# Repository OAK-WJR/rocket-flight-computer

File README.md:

# Rocket Flight Computer (M3, design only)

> **Status: design only. No board has been built, powered or flown.** Every result below comes from CAD checks, circuit simulation or software tests on a computer, never from hardware.

This is a flight computer for a student high-power rocket. It is one 46 × 238 mm, four-layer circuit board that slides into a 54.66 mm inside-diameter airframe. It runs from a 2-cell LiPo battery, uses an STM32H743 microcontroller, reads an IMU (ICM-45686), a barometer (MS5611) and GPS (SAM-M10Q), logs to flash memory, talks over USB, powers a camera, drives four fin servos for roll control, and has two separately fused circuits to fire the parachute charge. The current design is revision **M3-ASSY-R2** (28 Sep 2026).

*KiCad 3D render of the top side of M3-ASSY-R2 (46 × 238 mm).*

## Demo

There is no video, because the board has not been built. What can be shown and re-run today:

1. **Board checks.** `tools/check.sh` runs KiCad's design-rule check, electrical-rule check and schematic-vs-PCB check. Output on 2026-11-01 (KiCad 10.0.6):
   ```
   DRC violations 0  unconnected 0  schematic parity 0  ERC 0
   metadata / 3D model audit: OK
   ```
2. **Circuit simulation.** The ngspice suite in `m3_design/sim_r2/` found a flaw in the design: with a fresh 8.4 V battery, firing into a shorted igniter pulled the battery below 5 V for 3.9 ms (long enough that the computer could reset and miss the second parachute charge) and pushed 131 A through a transistor rated for 112 A. Adding a 2 Ω pulse resistor to each channel fixed it in simulation (4.1 A, battery stays above 8.2 V).

*Simulated, not measured. Grey: before the fix. Black: with the 2 Ω resistors. The 20 ms pulse length is a rule the future firmware must follow.*

The portfolio page for this project is 8a ("Rocket Flight Computer Design").

## How it works

```mermaid
flowchart LR
  BAT[2S LiPo battery] --> PWR[power switch, reverse and over-voltage protection, 3.3 V supply]
  PWR --> MCU[STM32H743 microcontroller]
  SEN[IMU, barometer, GPS] --> MCU
  MCU --> LOG[flash log]
  MCU --> USB[USB diagnostics]
  MCU --> CAM[camera power and UART]
  BAT --> ACT[actuator power switch]
  ACT --> SRV[four fin servos]
  ACT --> ARM[arming plug: a full break] --> PYRO[two fused parachute channels]
  MCU --> SRV
  MCU --> PYRO
```

- **One board instead of two.** An earlier version split the design into an M1 power/actuator board and an M2 microcontroller/sensor board joined by harnesses; M3 merges them back into one board (one assembly order, no 21-wire harness); the old M1 board is kept in `reference/m1_power_actuator/`.
- **Safety by hardware.** The arming plug is a complete electrical break in the parachute circuit; a script (`m3_design/check_actuators.py`) reads the PCB copper and fails if anything bypasses it.
- **Easy to diagnose.** Test pads, voltage-sense dividers and fault lines on the power rails; the bench firmware (for the previous revision R1) reports them over USB, and the host tools in `diagnostics/` turn a report into a list of likely faults.
- **Every part checked.** All BOM lines were checked against the maker's datasheet for pinout, land pattern, polarity and 3D orientation (`docs/R2_VERIFICATION.md`).

## How to run it

No hardware is needed for any of these. Tested on macOS with KiCad 10.0.6, ngspice 46 and Python 3.9 on 2026-11-01.

```bash
git clone https://github.com/OAK-WJR/rocket-flight-computer.git
cd rocket-flight-computer

tools/check.sh                          # DRC + ERC + schematic parity + 3D/metadata audit (needs KiCad 10.0.x)
python3 m3_design/check_actuators.py    # arming / pyro / servo safety contract -> "actuator safety contract: OK"
python3 m3_design/sim_r2/run.py         # ngspice suite -> {'PASS': 135, 'OLD-FAIL': 6, 'INFO': 8, 'DEMO': 2}
python3 m3_design/sim_r2/plot_short.py  # redraws docs/images/shorted_igniter_sim.png (needs matplotlib)
python3 tools/export_fab.py             # Gerber zip + JLCPCB BOM/CPL into m3_design/assembly_review/fab/

python3 -m venv .venv && .venv/bin/pip install -r diagnostics/requirements-lock.txt
.venv/bin/python -m unittest discover -s diagnostics -t . -p 'test_*.py'      # 173 tests, OK (1 skipped)
(cd m3_firmware && PYTHONPATH=.. python3 -m unittest test_firmware test_gnss test_usb)  # 41 tests, OK

open m3_design/assembly_review/m3.kicad_pro   # open the design in KiCad 10
```

- KiCad must be **10.0.x** (older versions cannot open the files). On Linux/Windows set `KICAD_CLI=/path/to/kicad-cli` before `tools/check.sh`.
- `OLD-FAIL` rows in the simulation are the pre-fix design, kept on purpose for comparison.
- **Firmware build:** `m3_firmware/build.py` needs the Arm GNU Toolchain 15.2.rel1 in `m3_firmware/toolchain/` and the maker datasheet PDFs it hash-checks (not committed, for copyright). It also refuses to build for R2 on purpose, because no R2 firmware exists yet. Prebuilt bench images for the older R1 board are in `m3_firmware/build_assembly_*/`. Do not run them on an R2 board.
- **To make a real board** you would order it from JLCPCB with the files from `tools/export_fab.py` (see `docs/ORDERING.md`), then need a 2S LiPo, an ST-Link/SWD probe and a USB-C cable. None of this has been done.

## Repo layout

| Path | What is in it |
|---|---|
| `m3_design/assembly_review/` | The KiCad 10 project (the single source of truth): 14 schematic sheets, PCB, local footprints, symbols and 3D models, schematic PNG/SVG exports in `sheets/`, review notes |
| `m3_design/sim_r2/` | ngspice suite for the actuator and parachute circuits (`run.py`, `RESULTS.md`, `FINDINGS.md`, `plot_short.py`) |
| `m3_design/check_actuators.py` | Safety check that reads the PCB netlist |
| `m3_firmware/` | Bench diagnostic firmware v0.8.1 (C, STM32 HAL + TinyUSB) for the R1 board, pin bindings, host-side tests |
| `diagnostics/` | Python host tools: USB/SWD readout, log recovery, fault localisation, test-point map |
| `docs/` | Ordering guide, part-by-part verification, actuator merge record, design rationale, FMEA, simulation notes, design history |
| `quality_audit/` | Board audit: conflicting part numbers, 3D model paths, DRC/ERC evidence |
| `reference/` | Older boards kept for comparison: M1 power/actuator board, M3-ASSY-R1 |
| `tools/` | `check.sh` (board gate), `export_fab.py` (fabrication files), JLCPCB stock and orientation helpers |
| `STATUS.md` | Every requirement and what is and is not verified |
| `AGENTS.md`, `CLAUDE.md` | The rules given to the AI coding assistants (see Credits) |

## Results and honest limits

What is done (on a computer only):
- KiCad DRC, ERC and schematic parity all at zero; 183 placed parts, every one with a JLCPCB/LCSC part code.
- 135 simulation checks pass for the current design; the shorted-igniter flaw was found and fixed in simulation.
- 173 host diagnostic tests and 41 firmware host tests pass.

What is not done:
- **Nothing has been ordered, built, powered, measured or flown.** Simulations use datasheet models, not measured parts.
- No firmware exists for R2. The firmware here is bench diagnostics for R1 only; it has no flight logic, servo control or parachute firing.
- Servo stall current through the board (about 7.7 A with all four stalled) is an estimate, not a measurement.
- Fit in the sled and airframe, the arming plug hardware and the external power switch are still open (`STATUS.md`, `docs/R2_VERIFICATION.md` §4).

Other branches: `m3-assy-r11` is the development line. It holds the later redesigns R3 to R10 (Oct 2026) and the compact R11 candidate (Nov 2026), committed by a collaborator, and the R10 bench diagnostics; each earlier revision is in its history. They are not part of the R2 design described here.

## Credits

**Jerry Wu (Jiarui Wu):** the project and its requirements: one board that fits the 54.66 mm airframe, built-in USB diagnostics, at most three PCB iterations. I chose to merge the two earlier boards into one, set the system constraints, made the design decisions recorded as "owner rulings" (for example two independently fused parachute channels, and keeping the backup altimeter fully separate), and reviewed the layout, flagging routing problems such as unwanted zigzag traces.

**AI coding assistants:** they produced most of the schematics, PCB layout, simulations, firmware and scripts from my requirements and decisions.
- **Claude Code** wrote the design documents, drew the first schematics through the EasyEDA API, wrote the KiCad board, routing and check scripts, and ran the ngspice simulations. It proposed and chose the 2 Ω per-channel pulse resistors shown above; I approved them. It also merged pull requests #1–#5 on my account, so those merge commits show my name.
- **Codex** did the quality audit, the single-board versions up to M3-ASSY-R1, the bench firmware v0.1–v0.8.1 and the USB diagnostic tools.
- Commits made with Claude Code carry a `Co-Authored-By: Claude` line. `AGENTS.md` (read by Codex, and by Claude Code through `CLAUDE.md`) holds the safety and routing rules they had to follow.

**Collaborator and existing work:**
- **Ethan Huang** (collaborator) merged the four servo outputs, the two fused parachute channels with the arming break, the pull-pin and the buzzer into the board (pull request #1, 26 Sep 2026), also with Claude Code. He committed the later R3–R10 branches.
- **Open-source code and models:** TinyUSB (MIT), STM32CubeH7 HAL (BSD-3-Clause) and CMSIS headers (Apache-2.0) in `m3_firmware/vendor/`; KiCad library 3D models (CC-BY-SA 4.0 with exception); footprints and 3D models converted from the EasyEDA/LCSC library with easyeda2kicad. Details and licences: [THIRD_PARTY_NOTICES.md](THIRD_PARTY_NOTICES.md).
- **Tools:** KiCad 10, ngspice, Python, Arm GNU Toolchain; part data from maker datasheets and LCSC/JLCPCB pages (linked in the review notes, not copied).

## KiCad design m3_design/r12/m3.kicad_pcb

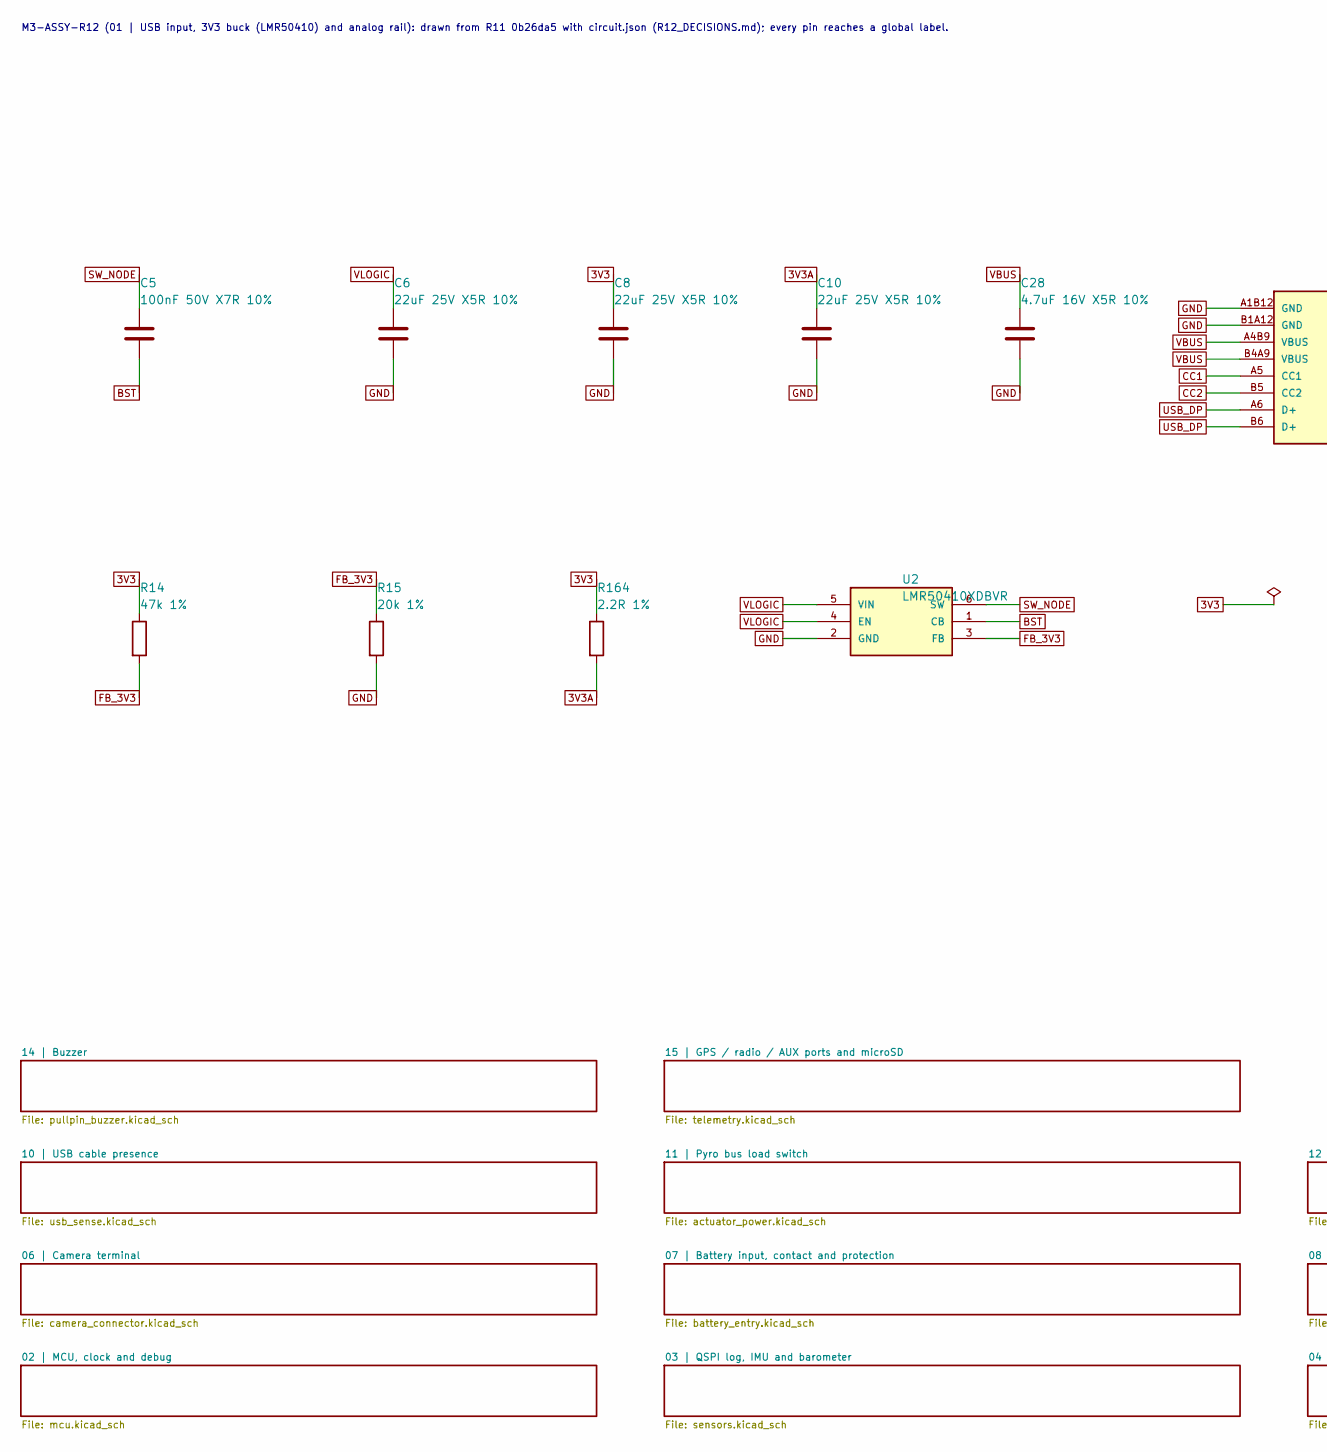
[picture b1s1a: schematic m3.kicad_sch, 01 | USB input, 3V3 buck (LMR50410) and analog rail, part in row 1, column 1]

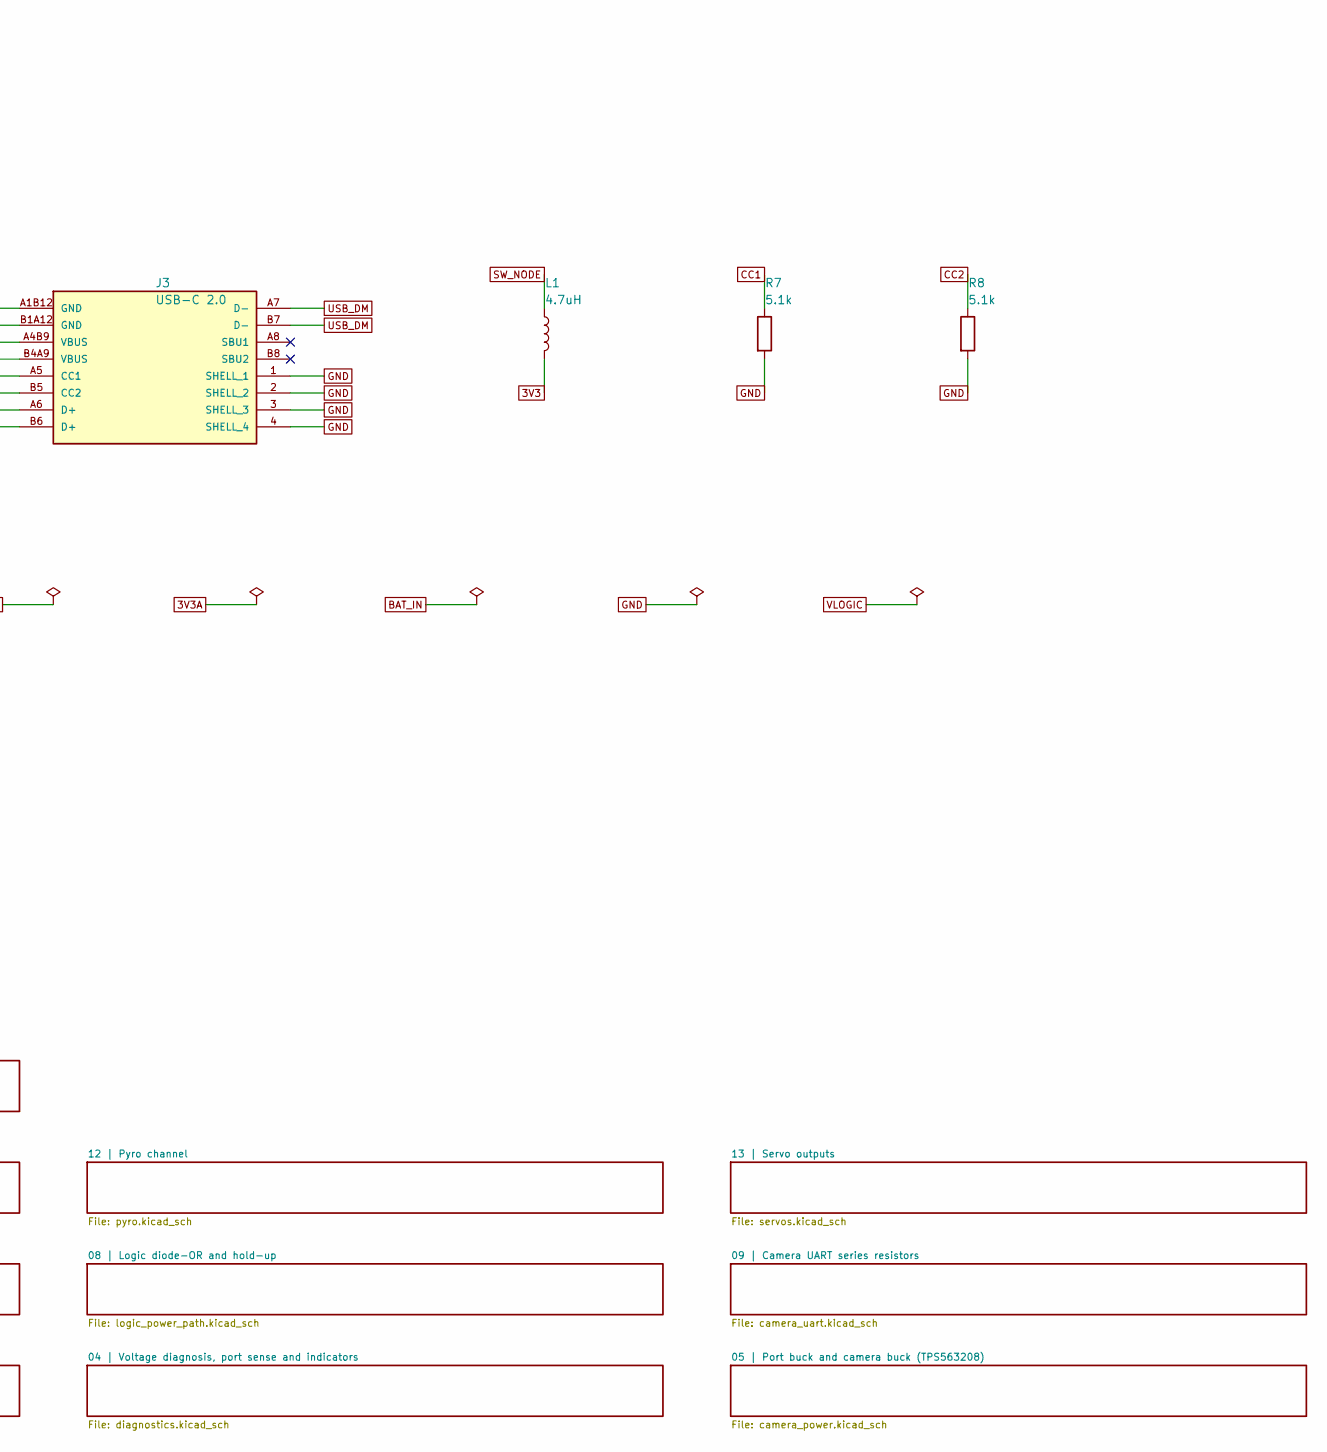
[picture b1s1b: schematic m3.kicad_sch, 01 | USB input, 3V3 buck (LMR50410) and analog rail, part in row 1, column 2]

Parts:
C5: 100nF 50V X7R 10%; C0402; Manufacturer Part CL05B104KB54PNC; LCSC C307331
C6, C8, C10: 22uF 25V X5R 10%; C_1206_3216Metric; Manufacturer Part CL31A226KAHNNNE; LCSC C12891
C28: 4.7uF 16V X5R 10%; C0603; Manufacturer Part CL10A475KO8NNNC; LCSC C19666
J3: USB-C 2.0; USB-C_SMD-TYPE-C-31-M-12_1; Manufacturer Part TYPE-C-31-M-12; LCSC C165948
L1: 4.7uH; IND-SMD_L4.0-W4.0; Manufacturer Part SWPA4030S4R7MT; LCSC C57269
R7, R8: 5.1k; R0402; Manufacturer Part 0402WGF5101TCE; LCSC C25905
R14: 47k 1%; R0402; Manufacturer Part 0402WGF4702TCE; LCSC C25792
R15: 20k 1%; R0402; Manufacturer Part 0402WGF2002TCE; LCSC C25765
R164: 2.2R 1%; R_0603_1608Metric; Manufacturer Part 0603WAF220KT5E; LCSC C22939
U2: LMR50410XDBVR; SOT-23-6_L2.9-W1.6-P0.95-LS2.8-BL; Manufacturer Part LMR50410XDBVR; LCSC C2841056

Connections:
3V3: C8.1, L1.2, R14.1, R164.1; also elsewhere on the board
3V3A: C10.1, R164.2; also elsewhere on the board
BST: C5.2, U2.1 (CB)
CC1: J3.A5 (CC1), R7.1
CC2: J3.B5 (CC2), R8.1
FB_3V3: R14.2, R15.1, U2.3 (FB)
GND: C6.2, C8.2, C10.2, C28.2, J3.1 (SHELL_1), J3.2 (SHELL_2), J3.3 (SHELL_3), J3.4 (SHELL_4), J3.A1B12 (GND), J3.B1A12 (GND), R7.2, R8.2, R15.2, U2.2 (GND); also elsewhere on the board
SW_NODE: C5.1, L1.1, U2.6 (SW)
USB_DM: J3.A7 (D-), J3.B7 (D-); also elsewhere on the board
USB_DP: J3.A6 (D+), J3.B6 (D+); also elsewhere on the board
VBUS: C28.1, J3.A4B9 (VBUS), J3.B4A9 (VBUS); also elsewhere on the board
VLOGIC: C6.1, U2.4 (EN), U2.5 (VIN); also elsewhere on the board

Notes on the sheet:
M3-ASSY-R12 (01 | USB input, 3V3 buck (LMR50410) and analog rail): drawn from R11 0b26da5 with circuit.json (R12_DECISIONS.md); every pin reaches a global label.

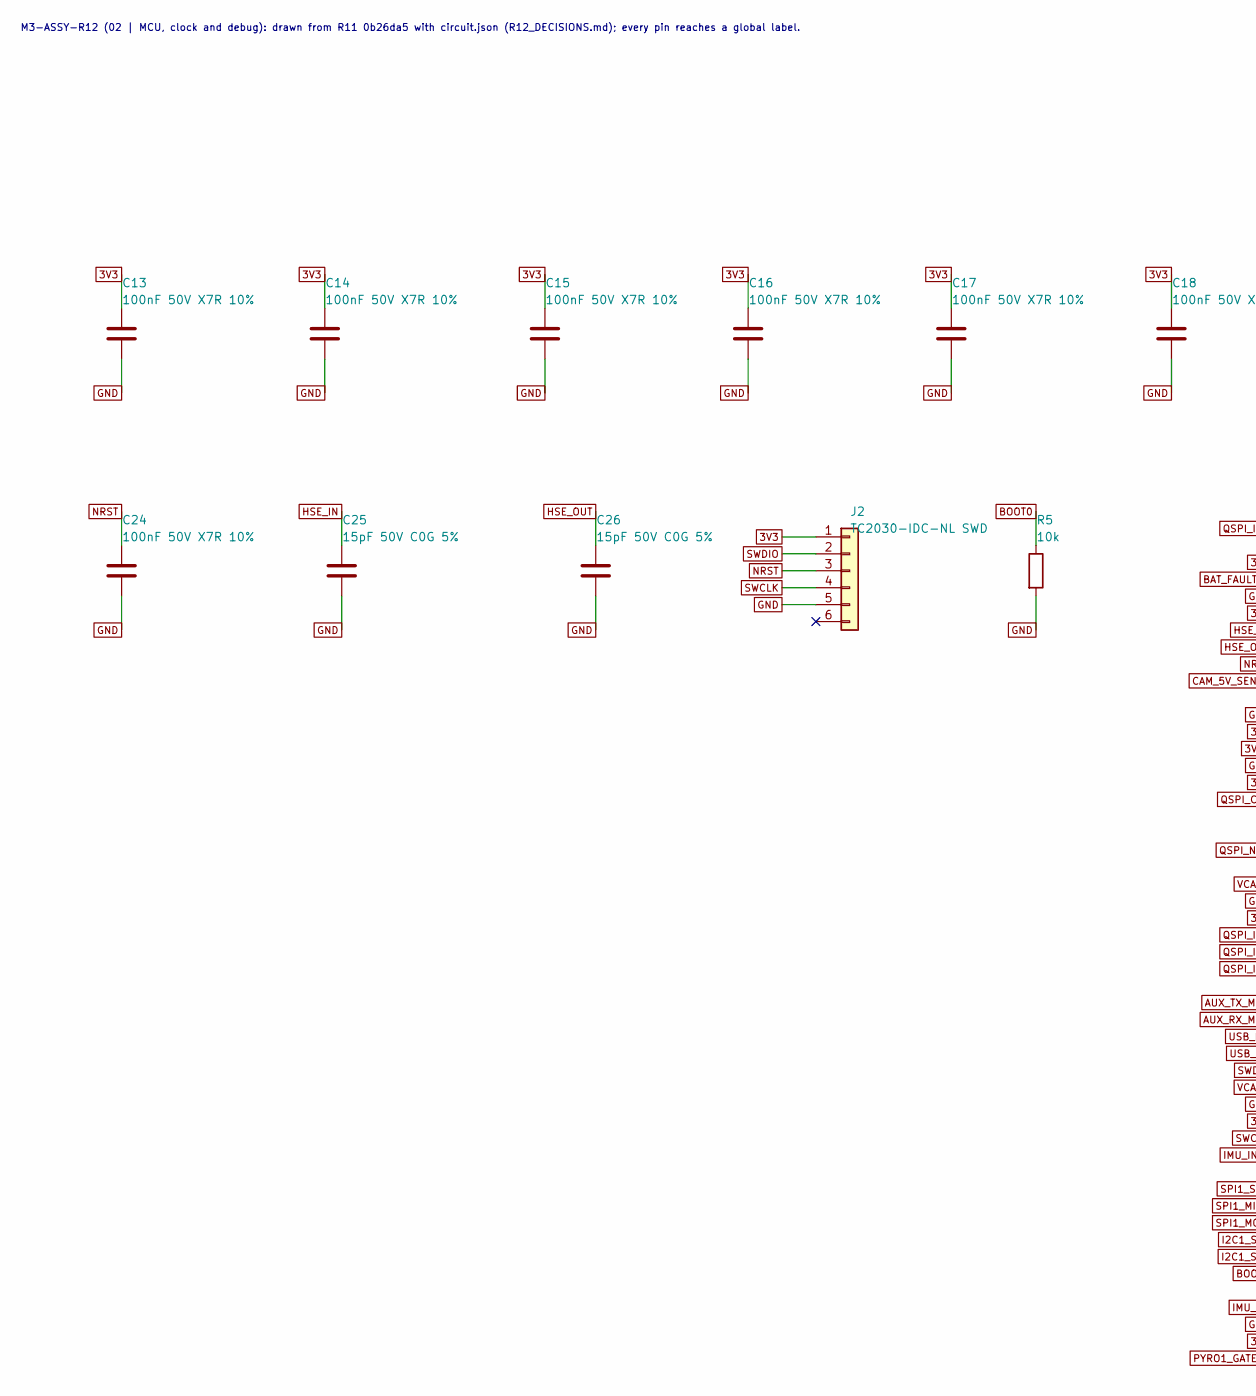
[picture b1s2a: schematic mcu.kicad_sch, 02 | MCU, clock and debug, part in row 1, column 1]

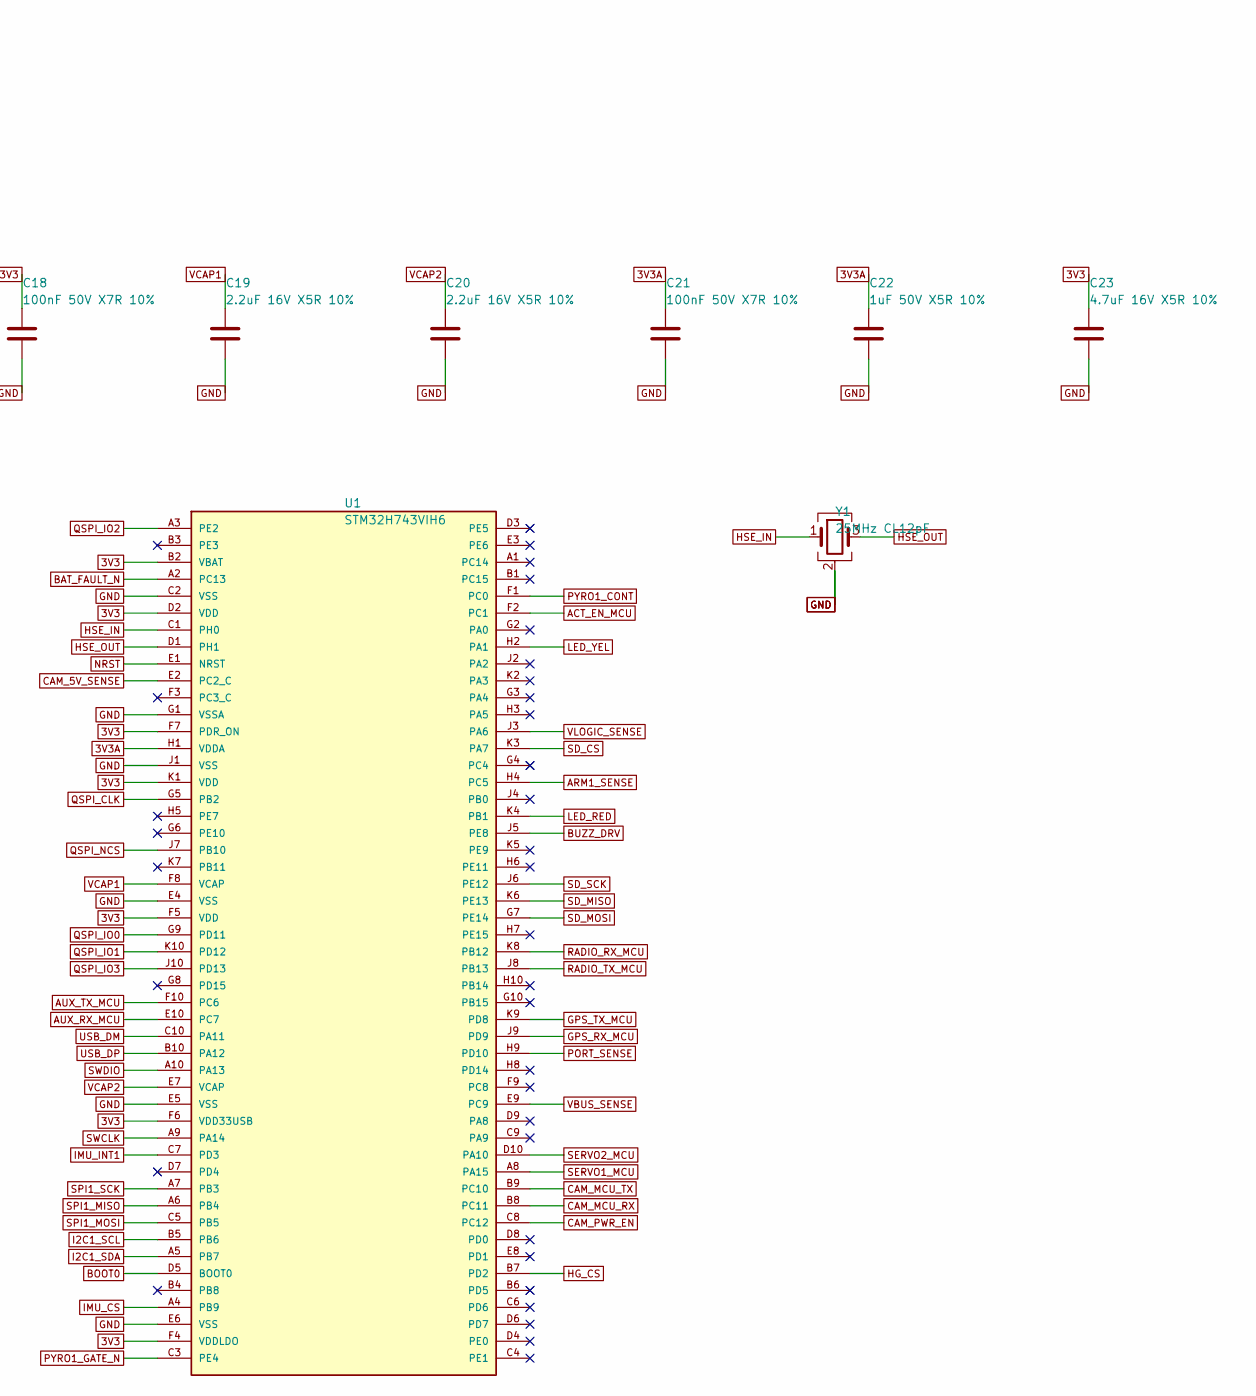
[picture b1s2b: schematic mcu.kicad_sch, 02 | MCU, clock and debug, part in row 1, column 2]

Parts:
C13, C14, C15, C16, C17, C18, C21, C24: 100nF 50V X7R 10%; C0402; Manufacturer Part CL05B104KB54PNC; LCSC C307331
C19, C20: 2.2uF 16V X5R 10%; C0603; Manufacturer Part CL10A225KO8NNNC; LCSC C23630
C22: 1uF 50V X5R 10%; C0603; Manufacturer Part CL10A105KB8NNNC; LCSC C15849
C23: 4.7uF 16V X5R 10%; C0603; Manufacturer Part CL10A475KO8NNNC; LCSC C19666
C25, C26: 15pF 50V C0G 5%; C0402; Manufacturer Part 0402CG150J500NT; LCSC C1548
J2: TC2030-IDC-NL SWD; M3_TC2030_IDC_NL; Manufacturer Part TC2030-IDC-NL
R5: 10k; R0402; Manufacturer Part 0402WGF1002TCE; LCSC C25744
U1: STM32H743VIH6; M3_TFBGA100_8x8_P0.8; Manufacturer Part STM32H743VIH6; LCSC C964146
Y1: 25MHz CL12pF; CRYSTAL-SMD_4P-L3.2-W2.5-BL; Manufacturer Part X322525MOB4SI; LCSC C9006

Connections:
3V3: C13.1, C14.1, C15.1, C16.1, C17.1, C18.1, C23.1, J2.1, U1.B2 (VBAT), U1.D2 (VDD), U1.F4 (VDDLDO), U1.F5 (VDD), U1.F6 (VDD33USB), U1.F7 (PDR_ON), U1.K1 (VDD); also elsewhere on the board
3V3A: C21.1, C22.1, U1.H1 (VDDA); also elsewhere on the board
ACT_EN_MCU: U1.F2 (PC1); also elsewhere on the board
ARM1_SENSE: U1.H4 (PC5); also elsewhere on the board
AUX_RX_MCU: U1.E10 (PC7); also elsewhere on the board
AUX_TX_MCU: U1.F10 (PC6); also elsewhere on the board
BAT_FAULT_N: U1.A2 (PC13); also elsewhere on the board
BOOT0: R5.1, U1.D5 (BOOT0)
BUZZ_DRV: U1.J5 (PE8); also elsewhere on the board
CAM_5V_SENSE: U1.E2 (PC2_C); also elsewhere on the board
CAM_MCU_RX: U1.B8 (PC11); also elsewhere on the board
CAM_MCU_TX: U1.B9 (PC10); also elsewhere on the board
CAM_PWR_EN: U1.C8 (PC12); also elsewhere on the board
GND: C13.2, C14.2, C15.2, C16.2, C17.2, C18.2, C19.2, C20.2, C21.2, C22.2, C23.2, C24.2, C25.2, C26.2, J2.5, R5.2, U1.C2 (VSS), U1.E4 (VSS), U1.E5 (VSS), U1.E6 (VSS), U1.G1 (VSSA), U1.J1 (VSS), Y1.2 (G), Y1.4 (G); also elsewhere on the board
GPS_RX_MCU: U1.J9 (PD9); also elsewhere on the board
GPS_TX_MCU: U1.K9 (PD8); also elsewhere on the board
HG_CS: U1.B7 (PD2); also elsewhere on the board
HSE_IN: C25.1, U1.C1 (PH0), Y1.1
HSE_OUT: C26.1, U1.D1 (PH1), Y1.3
I2C1_SCL: U1.B5 (PB6); also elsewhere on the board
I2C1_SDA: U1.A5 (PB7); also elsewhere on the board
IMU_CS: U1.A4 (PB9); also elsewhere on the board
IMU_INT1: U1.C7 (PD3); also elsewhere on the board
LED_RED: U1.K4 (PB1); also elsewhere on the board
LED_YEL: U1.H2 (PA1); also elsewhere on the board
NRST: C24.1, J2.3, U1.E1 (NRST)
PORT_SENSE: U1.H9 (PD10); also elsewhere on the board
PYRO1_CONT: U1.F1 (PC0); also elsewhere on the board
PYRO1_GATE_N: U1.C3 (PE4); also elsewhere on the board
QSPI_CLK: U1.G5 (PB2); also elsewhere on the board
QSPI_IO0: U1.G9 (PD11); also elsewhere on the board
QSPI_IO1: U1.K10 (PD12); also elsewhere on the board
QSPI_IO2: U1.A3 (PE2); also elsewhere on the board
QSPI_IO3: U1.J10 (PD13); also elsewhere on the board
QSPI_NCS: U1.J7 (PB10); also elsewhere on the board
RADIO_RX_MCU: U1.K8 (PB12); also elsewhere on the board
RADIO_TX_MCU: U1.J8 (PB13); also elsewhere on the board
SD_CS: U1.K3 (PA7); also elsewhere on the board
SD_MISO: U1.K6 (PE13); also elsewhere on the board
SD_MOSI: U1.G7 (PE14); also elsewhere on the board
SD_SCK: U1.J6 (PE12); also elsewhere on the board
SERVO1_MCU: U1.A8 (PA15); also elsewhere on the board
SERVO2_MCU: U1.D10 (PA10); also elsewhere on the board
SPI1_MISO: U1.A6 (PB4); also elsewhere on the board
SPI1_MOSI: U1.C5 (PB5); also elsewhere on the board
SPI1_SCK: U1.A7 (PB3); also elsewhere on the board
SWCLK: J2.4, U1.A9 (PA14)
SWDIO: J2.2, U1.A10 (PA13)
USB_DM: U1.C10 (PA11); also elsewhere on the board
USB_DP: U1.B10 (PA12); also elsewhere on the board
VBUS_SENSE: U1.E9 (PC9); also elsewhere on the board
VCAP1: C19.1, U1.F8 (VCAP)
VCAP2: C20.1, U1.E7 (VCAP)
VLOGIC_SENSE: U1.J3 (PA6); also elsewhere on the board

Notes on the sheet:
M3-ASSY-R12 (02 | MCU, clock and debug): drawn from R11 0b26da5 with circuit.json (R12_DECISIONS.md); every pin reaches a global label.

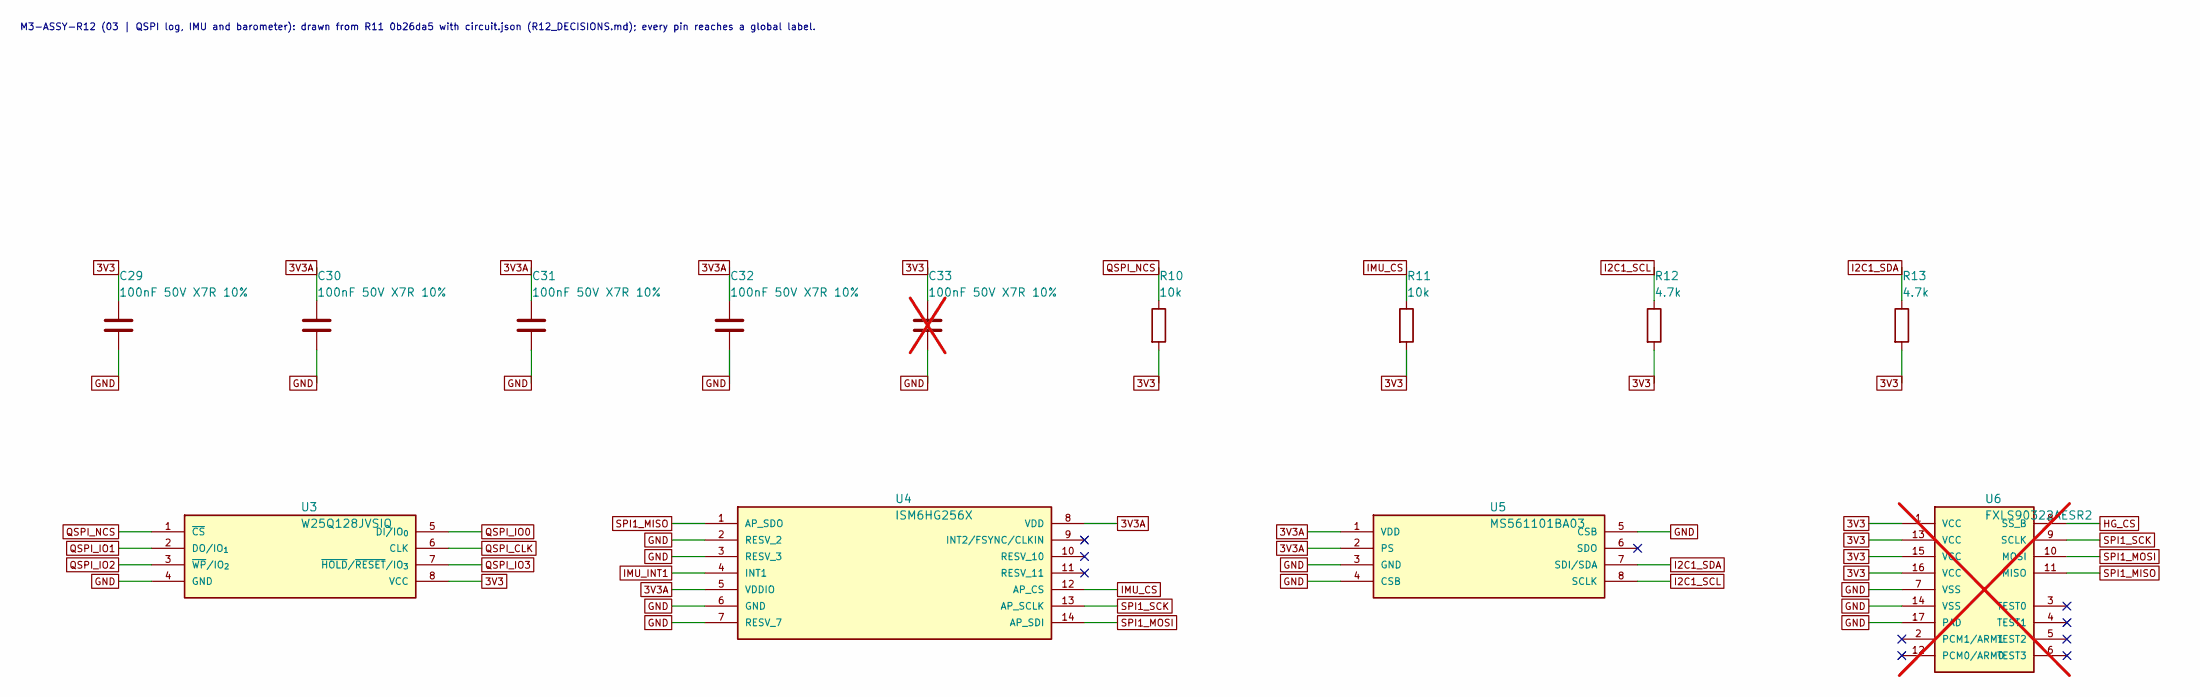
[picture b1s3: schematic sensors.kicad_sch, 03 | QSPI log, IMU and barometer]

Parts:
C29, C30, C31, C32: 100nF 50V X7R 10%; C0402; Manufacturer Part CL05B104KB54PNC; LCSC C307331
C33: 100nF 50V X7R 10%; C0402_DNP; Manufacturer Part CL05B104KB54PNC; LCSC C307331; not fitted
R10, R11: 10k; R0402; Manufacturer Part 0402WGF1002TCE; LCSC C25744
R12, R13: 4.7k; R0402; Manufacturer Part 0402WGF4701TCE; LCSC C25900
U3: W25Q128JVSIQ; SOIC-8_L5.3-W5.3-P1.27-LS8.0-BL; Manufacturer Part W25Q128JVSIQ; LCSC C97521
U4: ISM6HG256X; LGA-14_L3.0-W2.5-P0.50-TL; Manufacturer Part ISM6HG256XTR; LCSC C51931514
U5: MS561101BA03; SENSORS-SMD_MS5611-01BA03; Manufacturer Part MS561101BA03-50; LCSC C15639
U6: FXLS90322AESR2; M3_FXLS_HLQFN16_DNP; Manufacturer Part FXLS90322AESR2; LCSC C5190712; not fitted

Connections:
3V3: C29.1, C33.1, R10.2, R11.2, R12.2, R13.2, U3.8 (VCC), U6.1 (VCC), U6.13 (VCC), U6.15 (VCC), U6.16 (VCC); also elsewhere on the board
3V3A: C30.1, C31.1, C32.1, U4.5 (VDDIO), U4.8 (VDD), U5.1 (VDD), U5.2 (PS); also elsewhere on the board
GND: C29.2, C30.2, C31.2, C32.2, C33.2, U3.4 (GND), U4.2 (RESV_2), U4.3 (RESV_3), U4.6 (GND), U4.7 (RESV_7), U5.3 (GND), U5.4 (CSB), U5.5 (CSB), U6.7 (VSS), U6.14 (VSS), U6.17 (PAD); also elsewhere on the board
HG_CS: U6.8 (SS_B); also elsewhere on the board
I2C1_SCL: R12.1, U5.8 (SCLK); also elsewhere on the board
I2C1_SDA: R13.1, U5.7 (SDI/SDA); also elsewhere on the board
IMU_CS: R11.1, U4.12 (AP_CS); also elsewhere on the board
IMU_INT1: U4.4 (INT1); also elsewhere on the board
QSPI_CLK: U3.6 (CLK); also elsewhere on the board
QSPI_IO0: U3.5 (DI/IO_{0}); also elsewhere on the board
QSPI_IO1: U3.2 (DO/IO_{1}); also elsewhere on the board
QSPI_IO2: U3.3 (~WP/IO_{2}); also elsewhere on the board
QSPI_IO3: U3.7 (~HOLD/~RESET/IO_{3}); also elsewhere on the board
QSPI_NCS: R10.1, U3.1 (~CS); also elsewhere on the board
SPI1_MISO: U4.1 (AP_SDO), U6.11 (MISO); also elsewhere on the board
SPI1_MOSI: U4.14 (AP_SDI), U6.10 (MOSI); also elsewhere on the board
SPI1_SCK: U4.13 (AP_SCLK), U6.9 (SCLK); also elsewhere on the board

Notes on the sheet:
M3-ASSY-R12 (03 | QSPI log, IMU and barometer): drawn from R11 0b26da5 with circuit.json (R12_DECISIONS.md); every pin reaches a global label.

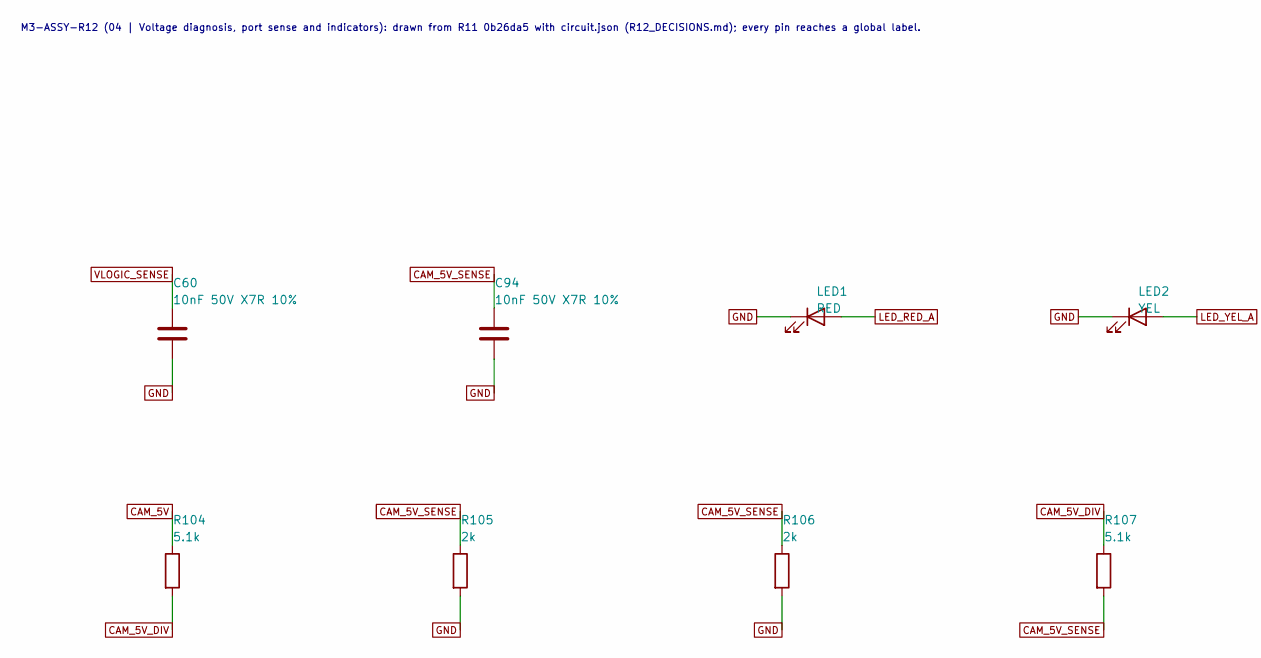
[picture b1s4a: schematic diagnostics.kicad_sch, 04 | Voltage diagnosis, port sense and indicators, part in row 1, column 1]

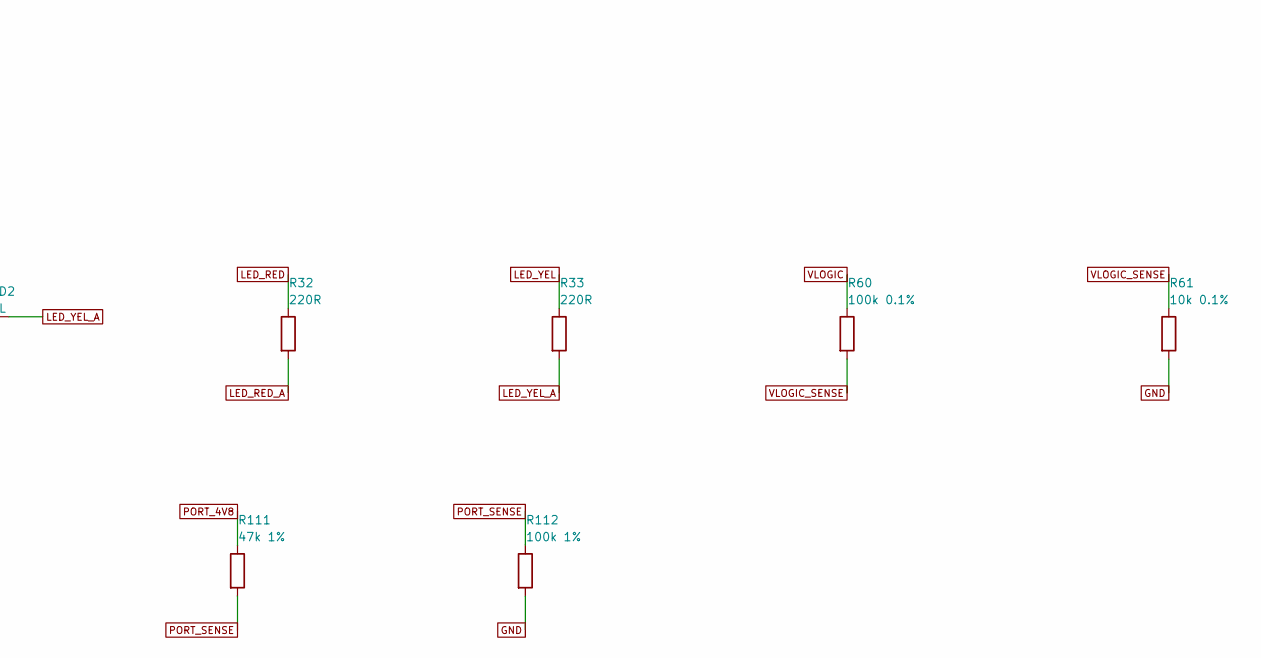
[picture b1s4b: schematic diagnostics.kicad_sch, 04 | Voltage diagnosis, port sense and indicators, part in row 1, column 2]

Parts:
C60, C94: 10nF 50V X7R 10%; C0402; Manufacturer Part CL05B103KB5NNNC; LCSC C15195
LED1: RED; M3_NCD0805R1_K1; Manufacturer Part NCD0805R1; LCSC C84256
LED2: YEL; M3_KT0805Y_A1; Manufacturer Part KT-0805Y; LCSC C2296
R32, R33: 220R; R0402; Manufacturer Part 0402WGF2200TCE; LCSC C25091
R60: 100k 0.1%; R0402; Manufacturer Part RT0402BRD07100KL; LCSC C852472
R61: 10k 0.1%; R0402; Manufacturer Part RT0402BRD0710KL; LCSC C190095
R104, R107: 5.1k; R0402; Manufacturer Part 0402WGF5101TCE; LCSC C25905
R105, R106: 2k; R0402; Manufacturer Part 0402WGF2001TCE; LCSC C4109
R111: 47k 1%; R0402; Manufacturer Part 0402WGF4702TCE; LCSC C25792
R112: 100k 1%; R0402; Manufacturer Part 0402WGF1003TCE; LCSC C25741

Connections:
CAM_5V: R104.1; also elsewhere on the board
CAM_5V_DIV: R104.2, R107.1
CAM_5V_SENSE: C94.1, R105.1, R106.1, R107.2; also elsewhere on the board
GND: C60.2, C94.2, LED1.1 (K), LED2.2 (K), R61.2, R105.2, R106.2, R112.2; also elsewhere on the board
LED_RED: R32.1; also elsewhere on the board
LED_RED_A: LED1.2 (A), R32.2
LED_YEL: R33.1; also elsewhere on the board
LED_YEL_A: LED2.1 (A), R33.2
PORT_4V8: R111.1; also elsewhere on the board
PORT_SENSE: R111.2, R112.1; also elsewhere on the board
VLOGIC: R60.1; also elsewhere on the board
VLOGIC_SENSE: C60.1, R60.2, R61.1; also elsewhere on the board

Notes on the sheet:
M3-ASSY-R12 (04 | Voltage diagnosis, port sense and indicators): drawn from R11 0b26da5 with circuit.json (R12_DECISIONS.md); every pin reaches a global label.

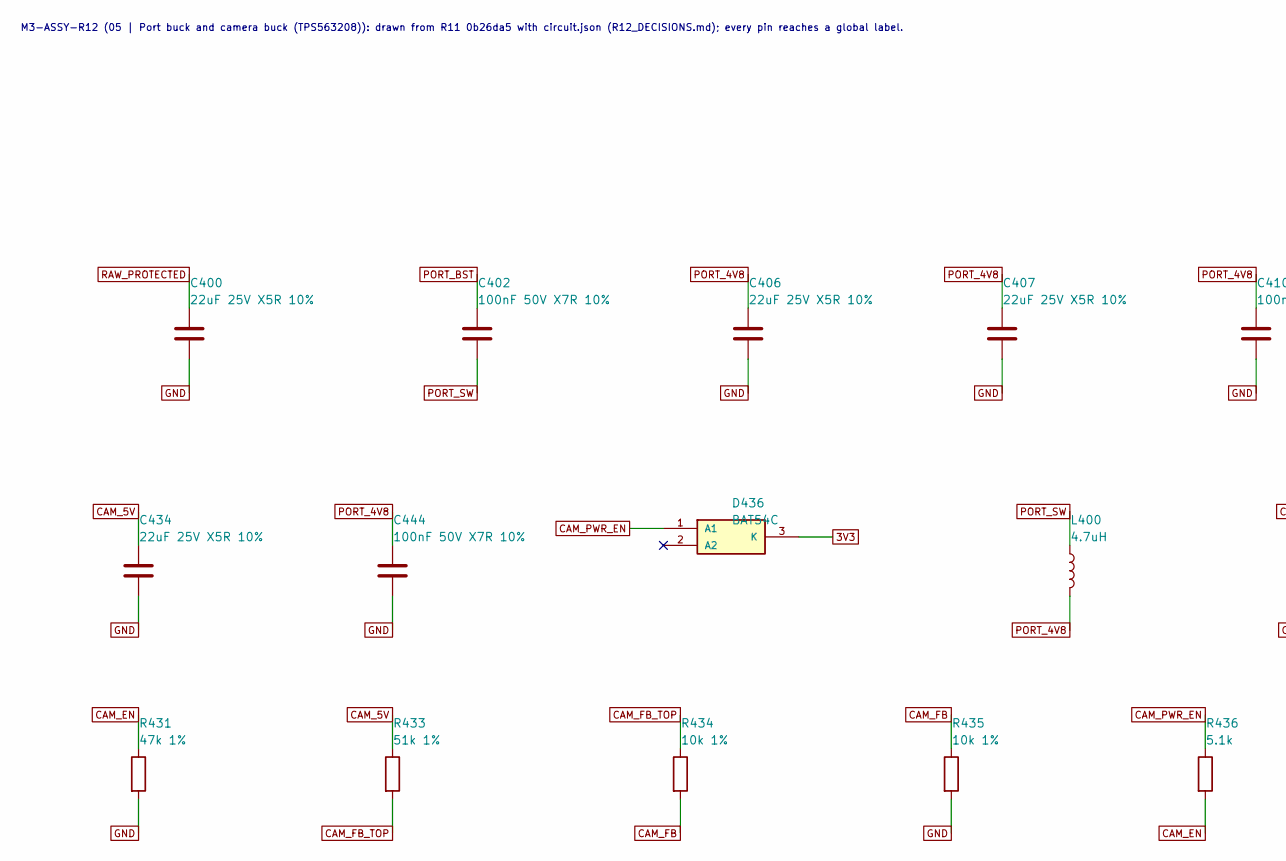
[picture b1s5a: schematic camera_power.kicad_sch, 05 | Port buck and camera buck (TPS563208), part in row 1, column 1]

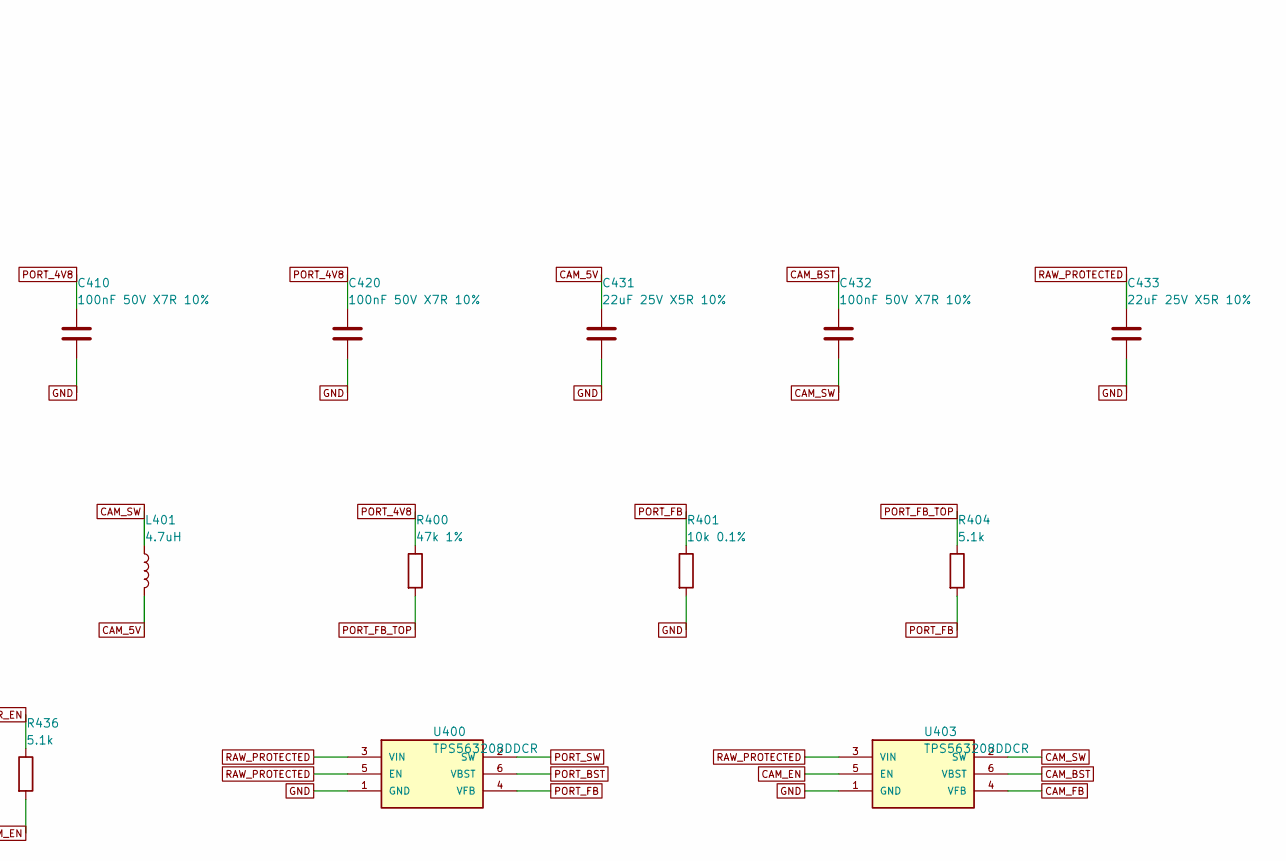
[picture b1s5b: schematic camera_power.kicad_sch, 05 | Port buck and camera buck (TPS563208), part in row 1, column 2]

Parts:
C400, C406, C407, C431, C433, C434: 22uF 25V X5R 10%; C_1206_3216Metric; Manufacturer Part CL31A226KAHNNNE; LCSC C12891
C402, C410, C420, C432, C444: 100nF 50V X7R 10%; C0402; Manufacturer Part CL05B104KB54PNC; LCSC C307331
D436: BAT54C; SOT-23-3_L2.9-W1.3-P1.90-LS2.4-BR; Manufacturer Part BAT54C,215; LCSC C37704
L400, L401: 4.7uH; IND-SMD_L4.0-W4.0; Manufacturer Part SWPA4030S4R7MT; LCSC C57269
R400, R431: 47k 1%; R0402; Manufacturer Part 0402WGF4702TCE; LCSC C25792
R401: 10k 0.1%; R0402; Manufacturer Part RT0402BRD0710KL; LCSC C190095
R404, R436: 5.1k; R0402; Manufacturer Part 0402WGF5101TCE; LCSC C25905
R433: 51k 1%; R0402; Manufacturer Part 0402WGF5102TCE; LCSC C25794
R434, R435: 10k 1%; R0402; Manufacturer Part 0402WGF1002TCE; LCSC C25744
U400, U403: TPS563208DDCR; M3_TSOT23_6_DDC; Manufacturer Part TPS563208DDCR; LCSC C468250

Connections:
3V3: D436.3 (K); also elsewhere on the board
CAM_5V: C431.1, C434.1, L401.2, R433.1; also elsewhere on the board
CAM_BST: C432.1, U403.6 (VBST)
CAM_EN: R431.1, R436.2, U403.5 (EN)
CAM_FB: R434.2, R435.1, U403.4 (VFB)
CAM_FB_TOP: R433.2, R434.1
CAM_PWR_EN: D436.1 (A1), R436.1; also elsewhere on the board
CAM_SW: C432.2, L401.1, U403.2 (SW)
GND: C400.2, C406.2, C407.2, C410.2, C420.2, C431.2, C433.2, C434.2, C444.2, R401.2, R431.2, R435.2, U400.1 (GND), U403.1 (GND); also elsewhere on the board
PORT_4V8: C406.1, C407.1, C410.1, C420.1, C444.1, L400.2, R400.1; also elsewhere on the board
PORT_BST: C402.1, U400.6 (VBST)
PORT_FB: R401.1, R404.2, U400.4 (VFB)
PORT_FB_TOP: R400.2, R404.1
PORT_SW: C402.2, L400.1, U400.2 (SW)
RAW_PROTECTED: C400.1, C433.1, U400.3 (VIN), U400.5 (EN), U403.3 (VIN); also elsewhere on the board

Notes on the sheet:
M3-ASSY-R12 (05 | Port buck and camera buck (TPS563208)): drawn from R11 0b26da5 with circuit.json (R12_DECISIONS.md); every pin reaches a global label.
